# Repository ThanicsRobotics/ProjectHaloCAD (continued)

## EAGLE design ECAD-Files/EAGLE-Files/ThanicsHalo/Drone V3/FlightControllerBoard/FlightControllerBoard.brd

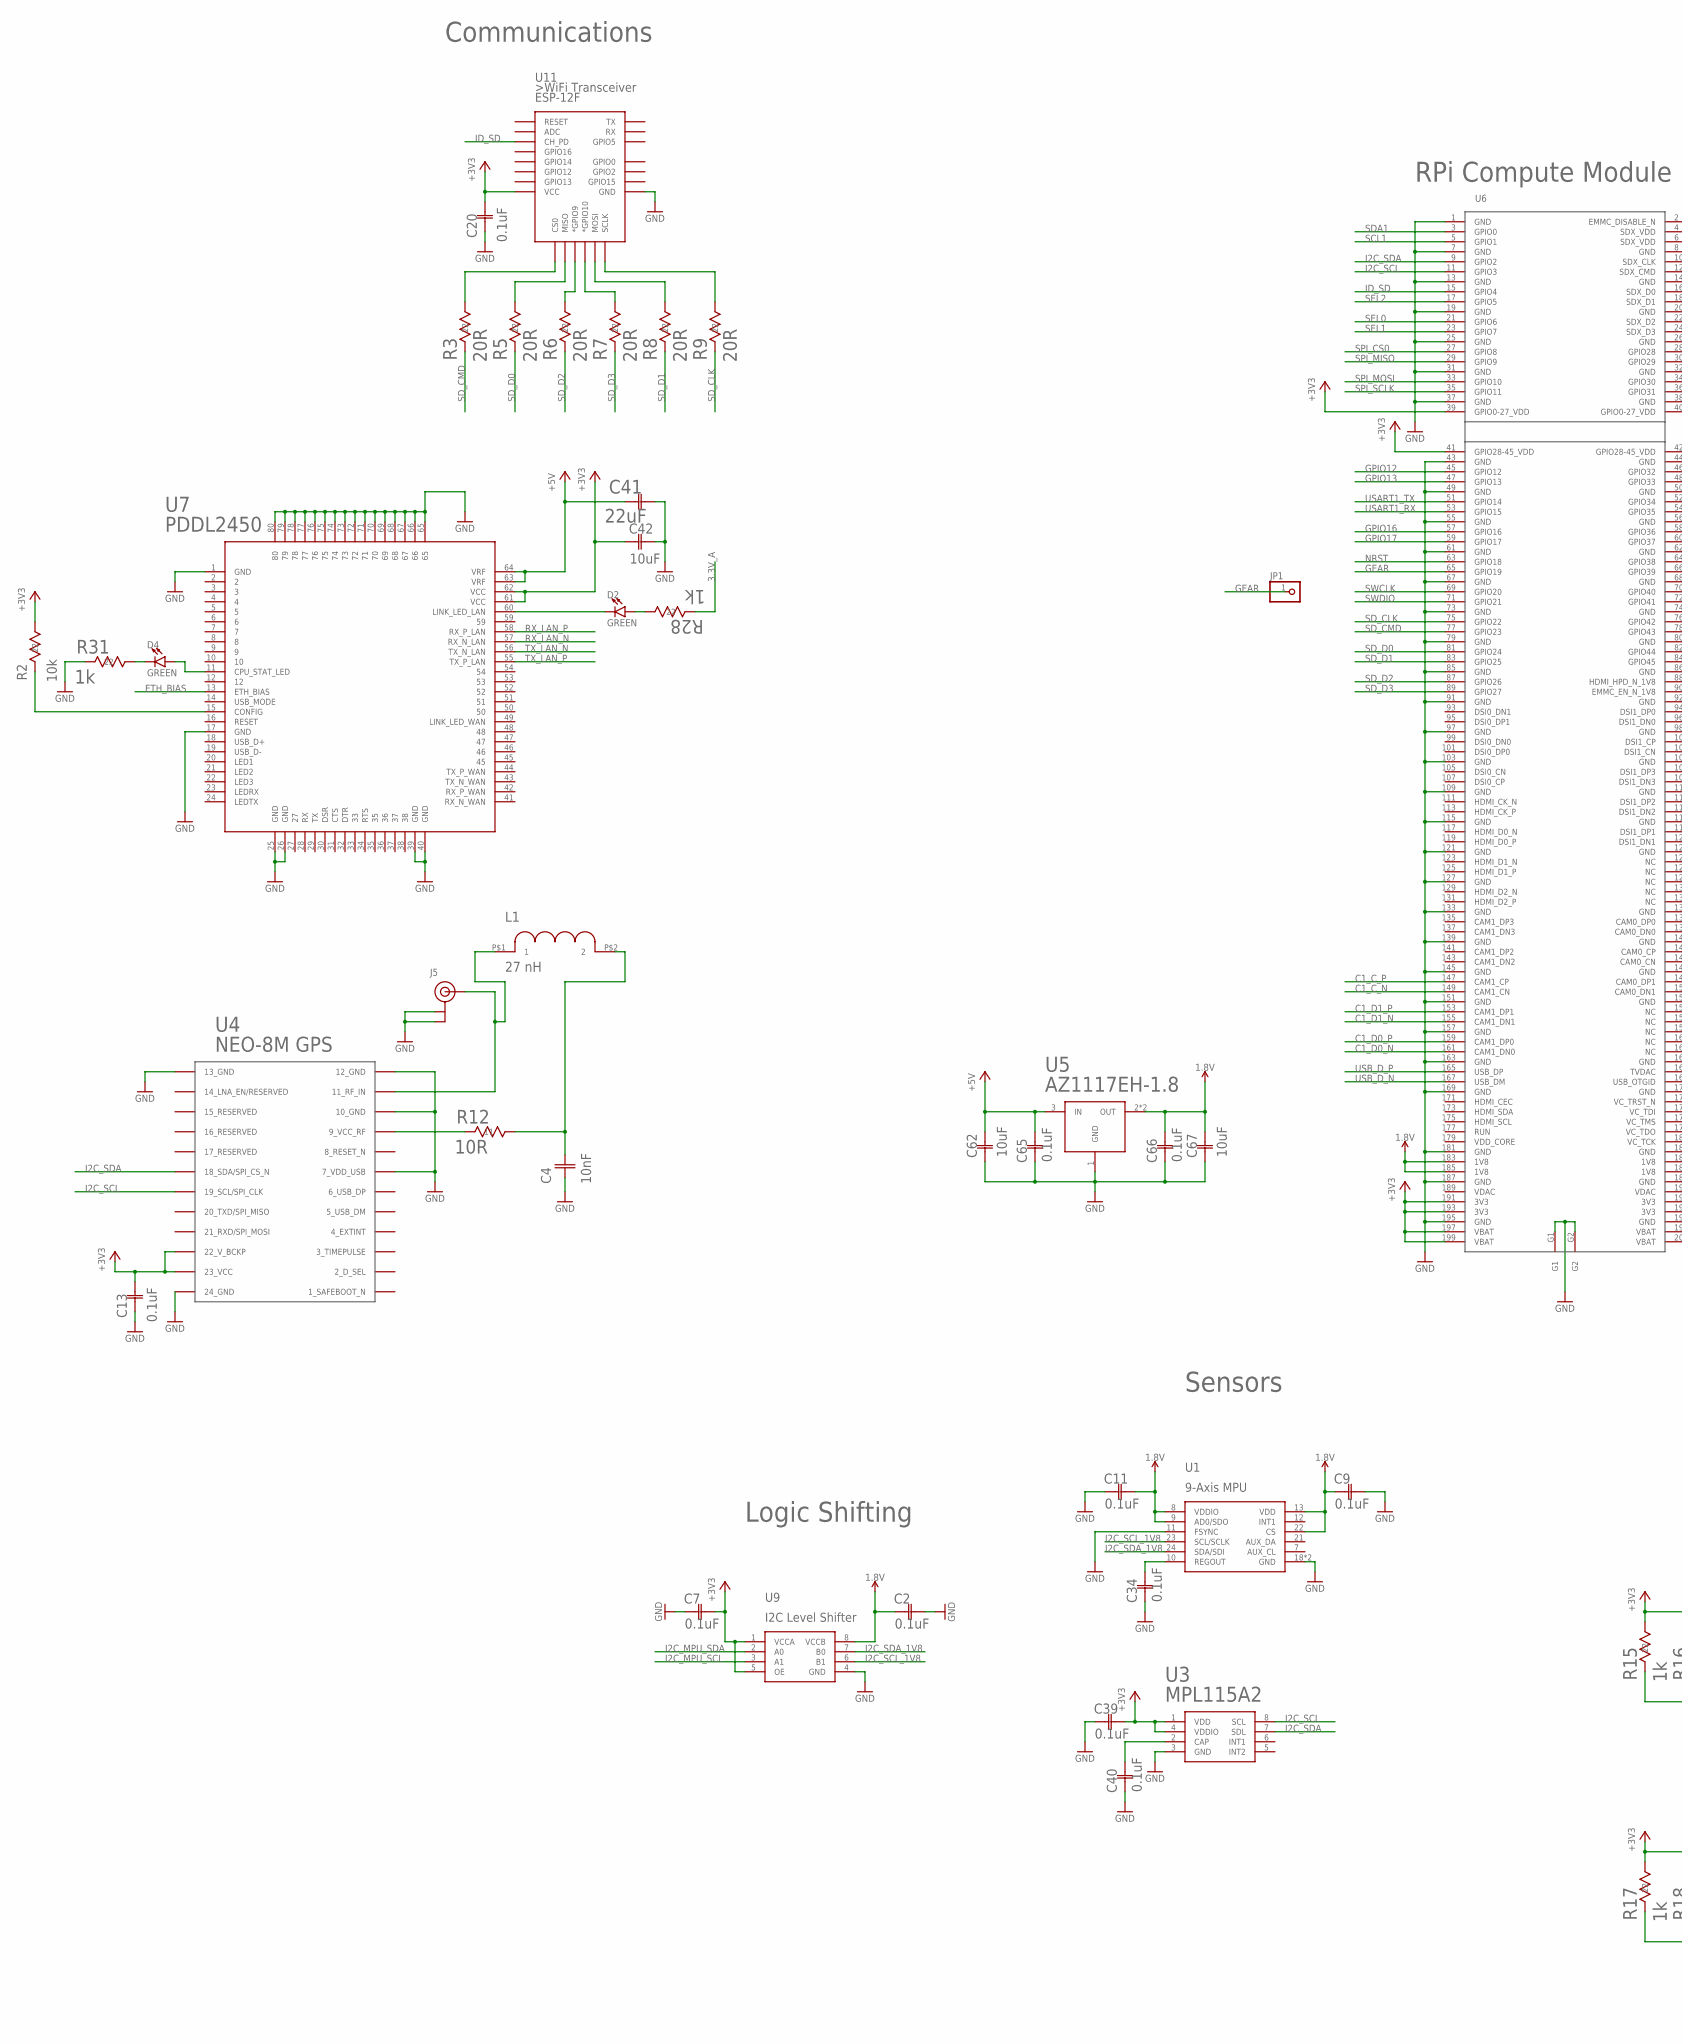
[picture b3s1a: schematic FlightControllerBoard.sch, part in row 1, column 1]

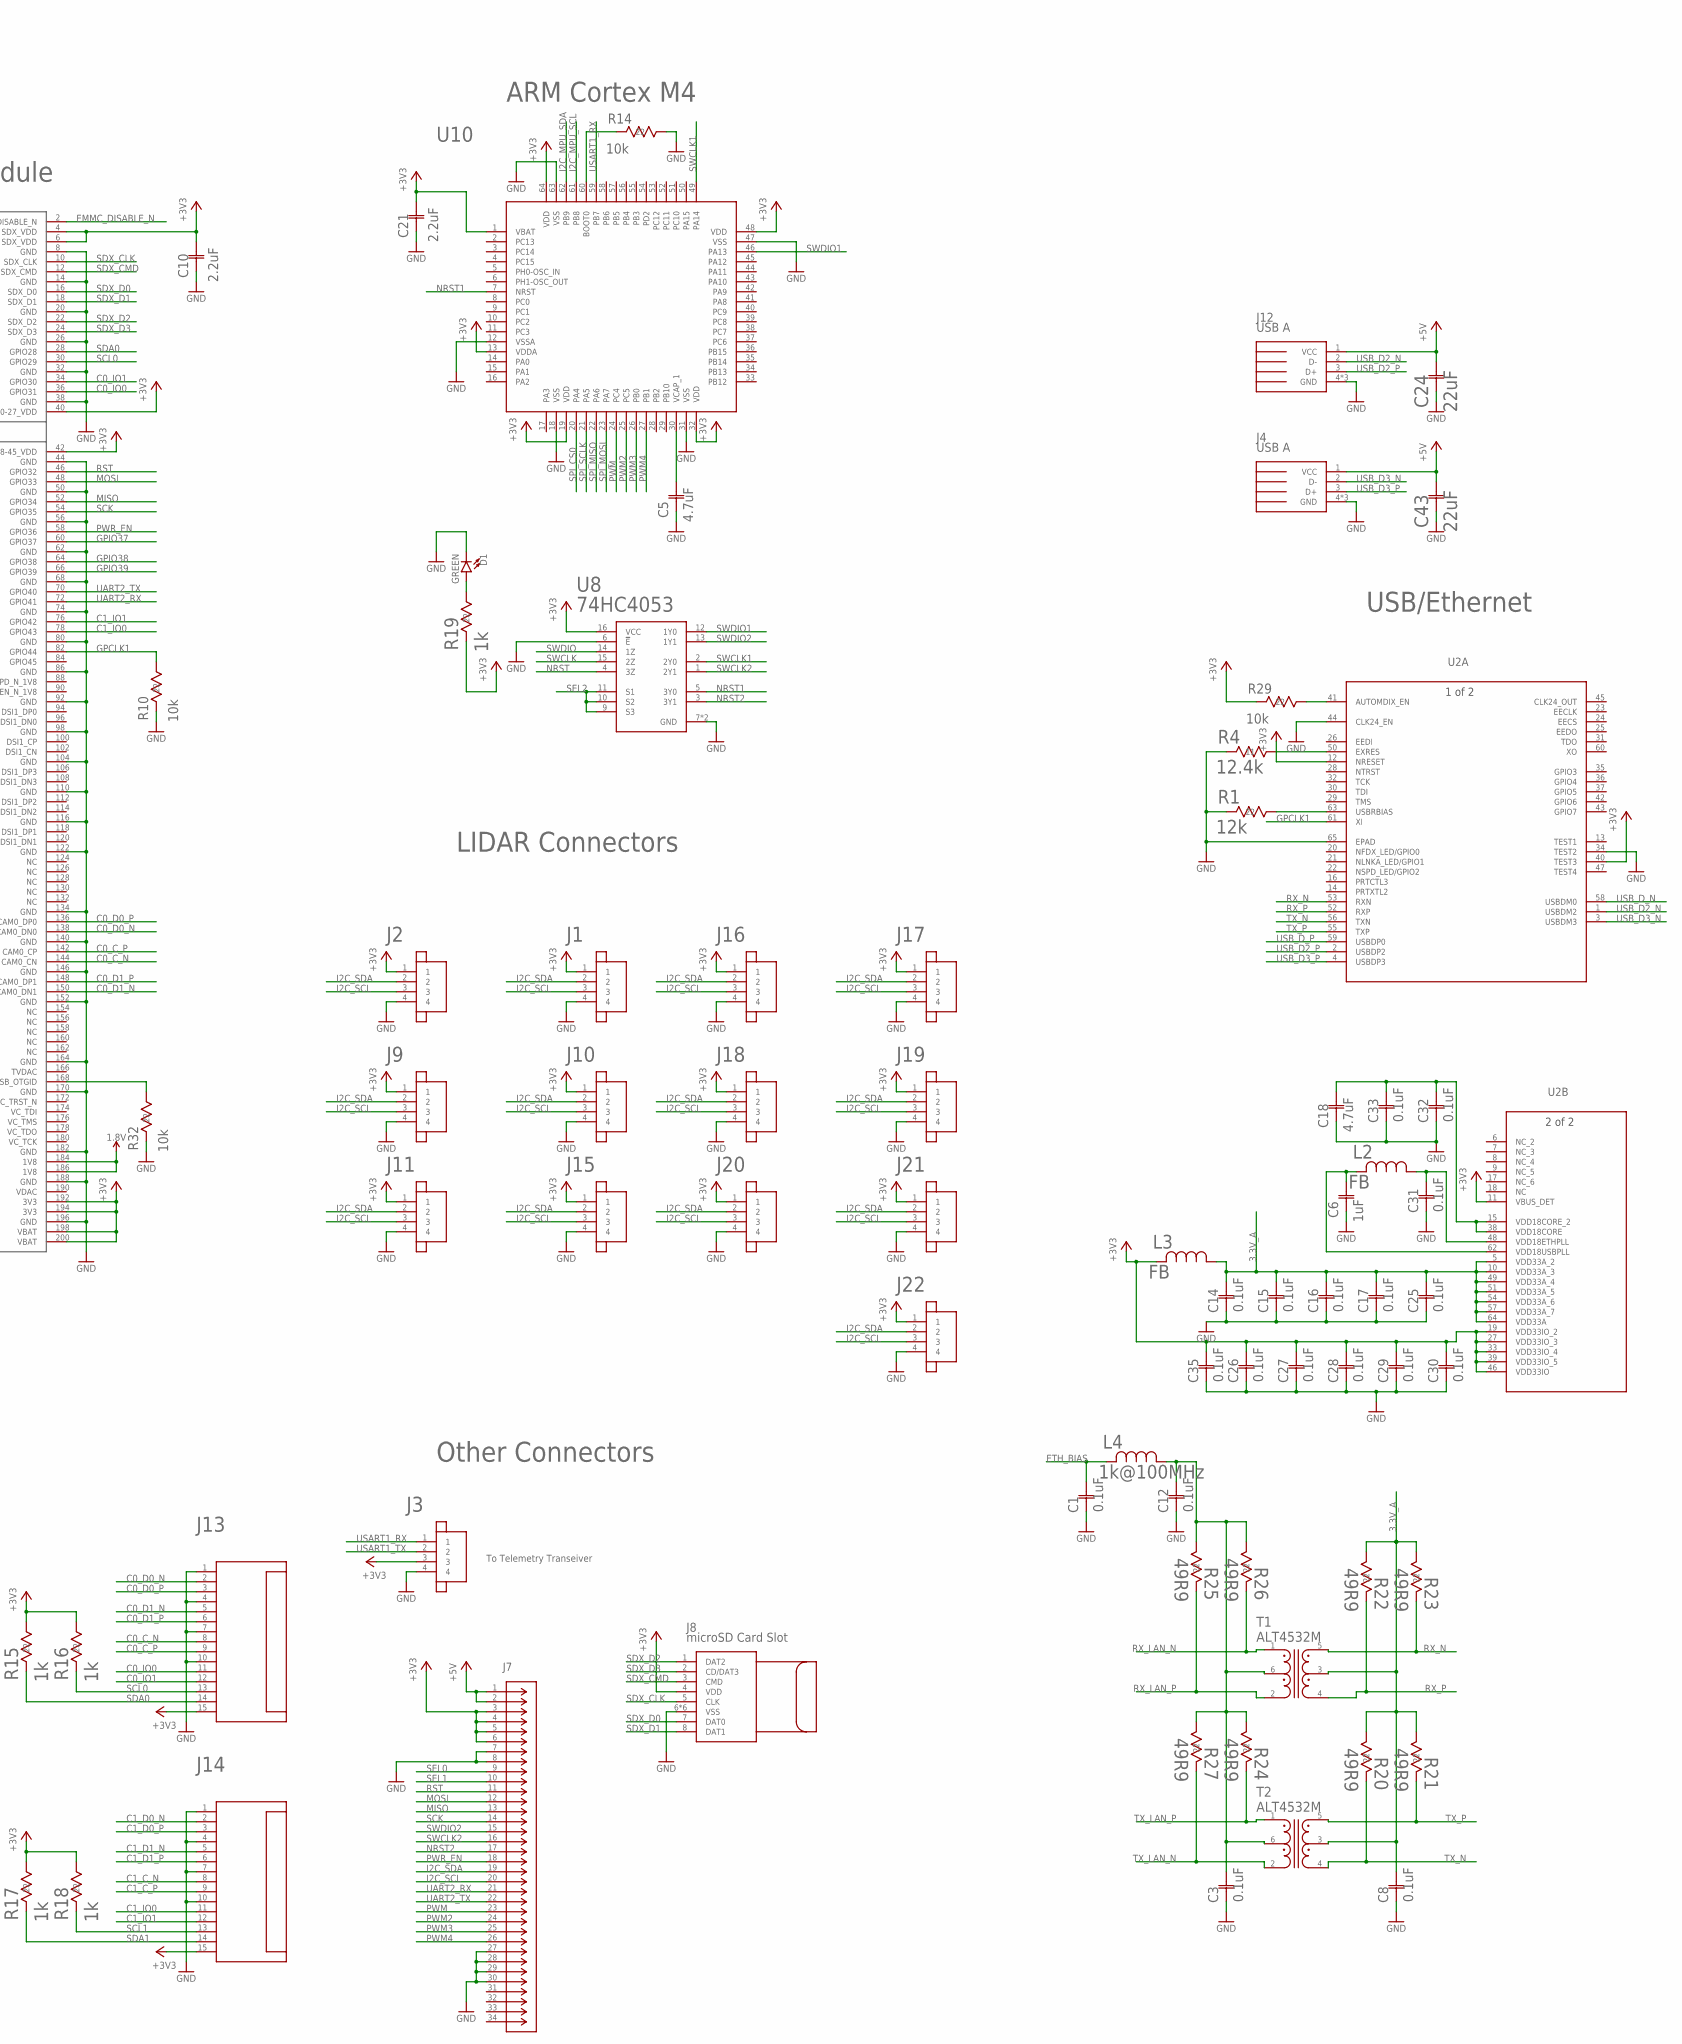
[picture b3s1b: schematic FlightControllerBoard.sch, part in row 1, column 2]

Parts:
C1, C2, C3, C7, C8, C9, C11, C12, C14, C15, C16, C17, C25, C26, C27, C28, C29, C30, C31, C32, C33, C34, C35, C39, C40, C65, C66: 0.1uF; 0402-M
C4: 10nF; 0603_CAPACITOR
C5, C18: 4.7uF; 0603-M
C6: 1uF; YAG_CC0805
C10, C21: 2.2uF; G-188-M
C13, C20: 0.1uF; 0805
C24, C41, C43: 22uF; G-21
C42, C62, C67: 10uF; G-21
D1, D2, D4: GREEN; LED-0603
J1, J2, J3, J9, J10, J11, J15, J16, J17, J18, J19, J20, J21, J22: JST_SH_4POS
J4, J12: UE27AE54100; USBA_RECEPT_VERT
J5: U.FL
J7: 62674-301121ALF; CON30_1X30_DUT_58XF
J8: MICROSD
J13, J14: 0526101572_15ZIF_CONNECTOR; 15POS_FFC_CONNECTOR
JP1: PINHD-1X1; 1X01
L1: 27 nH; 0402_INDUCTOR
L2, L3: FB; IND_BLM18_0603-M
L4: 1k@100MHz; IND_BLM18_0603-M
R1: 12k; RC0402N-M
R2, R10, R14, R29, R32: 10k; RC0603N-M
R3, R5, R6, R7, R8, R9: 20R; RC0603N-M
R4: 12.4k; YAG_R0402-M
R12: 10R; STA_RNCP0805-M
R15, R16, R17, R18, R19, R28, R31: 1k; RC0603N-M
R20, R21, R22, R23, R24, R25, R26, R27: 49R9; RC0402N-M
T1, T2: ALT4532M; ALT4532
U1: ICM-20948; QFN40P300X300X105-25N
U2: LAN9512-JZXQFN64_9X9MC-M; QFN64_9X9MC-M
U3: MPL115A2; LGA8-M
U4: NEO-M8
U5: AZ1117EH-1.8; SOT-223
U6: COMPUTE_MODULE; SO-DIMM
U7: PDDL2450; PDDL2450_SOCKET
U8: 74HC4053; TSSOP16
U9: FXMAR2102; 8-UMLP
U10: STM32F446; LQFP64
U11: ESP12ESMD; ESP12E-SMD

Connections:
1.8V: C2.1, C9.1, C11.2, C66.2, C67.2 (22), U1.8 (VDDIO), U1.9 (AD0/SDO), U1.13 (VDD), U1.22 (CS), U5.2 (OUT), U5.4 (OUT), U6.183 (1V8), U6.184 (1V8), U6.185 (1V8), U6.186 (1V8), U9.8 (VCCB)
3.3V_A: C8.2, C14.2, C15.2, C16.2, C17.2, C25.2, L3.1, R20.1 (11), R21.1 (11), R22.1 (11), R23.1 (11), R28.2 (22), T1.3, T2.3, U2.5 (VDD33A_2), U2.10 (VDD33A_3), U2.49 (VDD33A_4), U2.51 (VDD33A_5), U2.54 (VDD33A_6), U2.57 (VDD33A_7), U2.64 (VDD33A)
+3V3: C7.2, C10.2 (22), C13.2, C20.2, C21.2 (22), C26.2, C27.2, C28.2, C29.2, C30.2, C35.2, C39.2, C42.1 (11), J1.1, J2.1, J3.3, J7.3 (33), J7.4 (44), J7.5 (55), J7.6 (66), J8.4 (VDD), J9.1, J10.1, J11.1, J13.15, J14.15, J15.1, J16.1, J17.1, J18.1, J19.1, J20.1, J21.1, J22.1, L3.2, R2.1 (11), R15.1 (11), R16.1 (11), R17.1 (11), R18.1 (11), R19.2 (22), R29.2 (22), U2.11 (VBUS_DET), U2.12 (NRESET), U2.19 (VDD33IO_2), U2.27 (VDD33IO_3), U2.33 (VDD33IO_4), U2.39 (VDD33IO_5), U2.40 (TEST3), U2.46 (VDD33IO), U3.1 (VDD), U3.4 (VDDIO), U4.22 (22_V_BCKP), U4.23 (23_VCC), U6.4 (SDX_VDD), U6.6 (SDX_VDD), U6.39 (GPIO0-27_VDD), U6.40 (GPIO0-27_VDD), U6.41 (GPIO28-45_VDD), U6.42 (GPIO28-45_VDD), U6.191 (3V3), U6.192 (3V3), U6.193 (3V3), U6.194 (3V3), U6.197 (VBAT), U6.198 (VBAT), U6.199 (VBAT), U6.200 (VBAT), U7.61 (VCC), U7.62 (VCC), U8.16 (VCC), U9.1 (VCCA), U9.5 (OE), U10.1 (VBAT), U10.13 (VDDA), U10.19 (VDD), U10.32 (VDD), U10.48 (VDD), U10.64 (VDD), U11.VCC
+5V: C24.2 (22), C41.1 (11), C43.2 (22), C62.2 (22), C65.2, J4.1 (VCC), J7.1 (11), J7.2 (22), J12.1 (VCC), U5.3 (IN), U7.63 (VRF), U7.64 (VRF)
C0_C_N: J13.8, U6.144 (CAM0_CN)
C0_C_P: J13.9, U6.142 (CAM0_CP)
C0_D0_N: J13.2, U6.138 (CAM0_DN0)
C0_D0_P: J13.3, U6.136 (CAM0_DP0)
C0_D1_N: J13.5, U6.150 (CAM0_DN1)
C0_D1_P: J13.6, U6.148 (CAM0_DP1)
C0_IO0: J13.11, U6.36 (GPIO31)
C0_IO1: J13.12, U6.34 (GPIO30)
C1_C_N: J14.8, U6.149 (CAM1_CN)
C1_C_P: J14.9, U6.147 (CAM1_CP)
C1_D0_N: J14.2, U6.161 (CAM1_DN0)
C1_D0_P: J14.3, U6.159 (CAM1_DP0)
C1_D1_N: J14.5, U6.155 (CAM1_DN1)
C1_D1_P: J14.6, U6.153 (CAM1_DP1)
C1_IO0: J14.11, U6.78 (GPIO43)
C1_IO1: J14.12, U6.76 (GPIO42)
EMMC_DISABLE_N: U6.2 (EMMC_DISABLE_N)
ETH_BIAS: C1.2, L4.2, U7.13 (ETH_BIAS)
GEAR: JP1.1, U6.65 (GPIO19)
GND: C1.1, C2.2, C3.1, C4.1, C5.1, C6.1 (11), C7.1, C8.1, C9.2, C10.1 (11), C11.1, C12.1, C13.1, C14.1, C15.1, C16.1, C17.1, C18.1, C20.1, C21.1 (11), C24.1 (11), C25.1, C26.1, C27.1, C28.1, C29.1, C30.1, C31.1, C32.1, C33.1, C34.1, C35.1, C39.1, C40.1, C41.2 (22), C42.2 (22), C43.1 (11), C62.1 (11), C65.1, C66.1, C67.1 (11), D1.C, J1.4, J2.4, J3.4, J4.4 (GND), J4.P$5 (GND), J4.P$6 (GND), J5.P$1 (GND), J5.P$2 (GND), J7.7 (77), J7.8 (88), J7.27 (2727), J7.28 (2828), J7.29 (2929), J7.30 (3030), J8.6 (VSS), J8.9 (VSS), J8.10 (VSS), J8.11 (VSS), J8.12 (VSS), J8.13 (VSS), J9.4, J10.4, J11.4, J12.4 (GND), J12.P$5 (GND), J12.P$6 (GND), J13.1, J13.4, J13.7, J13.10, J14.1, J14.4, J14.7, J14.10, J15.4, J16.4, J17.4, J18.4, J19.4, J20.4, J21.4, J22.4, R1.2 (22), R4.1 (11), R10.2 (22), R14.1 (11), R31.2 (22), R32.2 (22), U1.11 (FSYNC), U1.18 (GND), U1.20 (GND), U2.34 (TEST2), U2.44 (CLK24_EN), U2.65 (EPAD), U3.3 (GND), U4.7 (7_VDD_USB), U4.10 (10_GND), U4.12 (12_GND), U4.13 (13_GND), U4.24 (24_GND), U5.1 (GND), U6.1 (GND), U6.7 (GND), U6.8 (GND), U6.13 (GND), U6.14 (GND), U6.19 (GND), U6.20 (GND), U6.25 (GND), U6.26 (GND), U6.31 (GND), U6.32 (GND), U6.37 (GND), U6.38 (GND), U6.43 (GND), U6.44 (GND), U6.49 (GND), U6.50 (GND), U6.55 (GND), U6.56 (GND), U6.61 (GND), U6.62 (GND), U6.67 (GND), U6.68 (GND), U6.73 (GND), U6.74 (GND), U6.79 (GND), U6.80 (GND), U6.85 (GND), U6.86 (GND), U6.91 (GND), U6.92 (GND), U6.97 (GND), U6.98 (GND), U6.103 (GND), U6.104 (GND), U6.109 (GND), U6.110 (GND), U6.115 (GND), U6.116 (GND), U6.121 (GND), U6.122 (GND), U6.127 (GND), U6.133 (GND), U6.134 (GND), U6.139 (GND), U6.140 (GND), U6.145 (GND), U6.146 (GND), U6.151 (GND), U6.152 (GND), U6.157 (GND), U6.163 (GND), U6.164 (GND), U6.169 (GND), U6.170 (GND), U6.181 (GND), U6.182 (GND), U6.187 (GND), U6.188 (GND), U6.195 (GND), U6.196 (GND), U6.G1, U6.G2, U7.1 (GND), U7.17 (GND), U7.25 (GND), U7.26 (GND), U7.39 (GND), U7.40 (GND), U7.65, U7.66, U7.67, U7.68, U7.69, U7.70, U7.71, U7.72, U7.73, U7.74, U7.75, U7.76, U7.77, U7.78, U7.79, U7.80, U8.6 (!E), U8.7 (GND), U8.8 (GND), U9.4 (GND), U10.12 (VSSA), U10.18 (VSS), U10.31 (VSS), U10.47 (VSS), U10.63 (VSS), U11.GND
GND1: D2.C, U7.60 (LINK_LED_LAN)
GPCLK1: R10.1 (11), U2.61 (XI), U6.82 (GPIO44)
GPIO12: U6.45 (GPIO12)
GPIO13: U6.47 (GPIO13)
GPIO16: U6.57 (GPIO16)
GPIO17: U6.59 (GPIO17)
GPIO37: U6.60 (GPIO37)
GPIO38: U6.64 (GPIO38)
GPIO39: U6.66 (GPIO39)
I2C_MPU_SCL: U9.3 (A1), U10.61 (PB8)
I2C_MPU_SDA: U9.2 (A0), U10.62 (PB9)
I2C_SCL: J1.3, J2.3, J7.20 (2020), J9.3, J10.3, J11.3, J15.3, J16.3, J17.3, J18.3, J19.3, J20.3, J21.3, J22.3, U3.8 (SCL), U4.19 (19_SCL/SPI_CLK), U6.11 (GPIO3)
I2C_SCL_1V8: U1.23 (SCL/SCLK), U9.6 (B1)
I2C_SDA: J1.2, J2.2, J7.19 (1919), J9.2, J10.2, J11.2, J15.2, J16.2, J17.2, J18.2, J19.2, J20.2, J21.2, J22.2, U3.7 (SDL), U4.18 (18_SDA/SPI_CS_N), U6.9 (GPIO2)
I2C_SDA_1V8: U1.24 (SDA/SDI), U9.7 (B0)
ID_SD: U6.15 (GPIO4), U11.CH_PD
MISO: J7.13 (1313), U6.52 (GPIO34)
MOSI: J7.12 (1212), U6.48 (GPIO33)
unnamed: J5.P$3 (SIGNAL), L1.P$1 (1), U4.11 (11_RF_IN)
unnamed: C34.2, U1.10 (REGOUT)
unnamed: R29.1 (11), U2.41 (AUTOMDIX_EN)
unnamed: D1.A, R19.1 (11)
unnamed: R1.1 (11), U2.63 (USBRBIAS)
unnamed: C40.2, U3.2 (CAP)
unnamed: R3.1 (11), U11.CS0
unnamed: R5.1 (11), U11.MISO
unnamed: R6.1 (11), U11.GPIO9 (*GPIO9)
unnamed: R7.1 (11), U11.GPIO10 (*GPIO10)
unnamed: C5.2, U10.30 (VCAP_1)
unnamed: D2.A, R28.1 (11)
unnamed: R12.1 (11), U4.9 (9_VCC_RF)
unnamed: R8.1 (11), U11.MOSI
unnamed: R9.1 (11), U11.SCLK
unnamed: R14.2 (22), U10.60 (BOOT0)
unnamed: C31.2, L2.1, U2.48 (VDD18ETHPLL)
unnamed: C6.2 (22), L2.2, U2.62 (VDD18USBPLL)
unnamed: R4.2 (22), U2.50 (EXRES)
unnamed: C18.2, C32.2, C33.2, U2.15 (VDD18CORE_2), U2.38 (VDD18CORE)
unnamed: C3.2, C12.2, L4.1, R24.1 (11), R25.1 (11), R26.1 (11), R27.1 (11), T1.6, T2.6
unnamed: R2.2 (22), U7.15 (CONFIG)
unnamed: D4.A, U7.11 (CPU_STAT_LED)
unnamed: C4.2, L1.P$2 (2), R12.2 (22)
unnamed: D4.C, R31.1 (11)
unnamed: R32.1 (11), U6.168 (USB_OTGID)
NRST: U6.63 (GPIO18), U8.4 (3Z)
NRST1: U8.5 (3Y0), U10.7 (NRST)
NRST2: J7.17 (1717), U8.3 (3Y1)
PWM: J7.23 (2323), U10.24 (PC4)
PWM2: J7.24 (2424), U10.25 (PC5)
PWM3: J7.25 (2525), U10.26 (PB0)
PWM4: J7.26 (2626), U10.27 (PB1)
PWR_EN: J7.18 (1818), U6.58 (GPIO36)
RST: J7.11 (1111), U6.46 (GPIO32)
RX_LAN_N: R26.2 (22), T1.1, U7.57 (RX_N_LAN)
RX_LAN_P: R25.2 (22), T1.2, U7.58 (RX_P_LAN)
RX_N: R23.2 (22), T1.5, U2.53 (RXN)
RX_P: R22.2 (22), T1.4, U2.52 (RXP)
SCK: J7.14 (1414), U6.54 (GPIO35)
SCL0: J13.13, R16.2 (22), U6.30 (GPIO29)
SCL1: J14.13, R18.2 (22), U6.5 (GPIO1)
SDA0: J13.14, R15.2 (22), U6.28 (GPIO28)
SDA1: J14.14, R17.2 (22), U6.3 (GPIO0)
SDX_CLK: J8.5 (CLK), U6.10 (SDX_CLK)
SDX_CMD: J8.3 (CMD), U6.12 (SDX_CMD)
SDX_D0: J8.7 (DAT0), U6.16 (SDX_D0)
SDX_D1: J8.8 (DAT1), U6.18 (SDX_D1)
SDX_D2: J8.1 (DAT2), U6.22 (SDX_D2)
SDX_D3: J8.2 (CD/DAT3), U6.24 (SDX_D3)
SD_CLK: R9.2 (22), U6.75 (GPIO22)
SD_CMD: R3.2 (22), U6.77 (GPIO23)
SD_D0: R5.2 (22), U6.81 (GPIO24)
SD_D1: R8.2 (22), U6.83 (GPIO25)
SD_D2: R6.2 (22), U6.87 (GPIO26)
SD_D3: R7.2 (22), U6.89 (GPIO27)
SEL0: J7.9 (99), U6.21 (GPIO6)
SEL1: J7.10 (1010), U6.23 (GPIO7)
SEL2: U6.17 (GPIO5), U8.9 (S3), U8.10 (S2), U8.11 (S1)
SPI_CS0: U6.27 (GPIO8), U10.20 (PA4)
SPI_MISO: U6.29 (GPIO9), U10.22 (PA6)
SPI_MOSI: U6.33 (GPIO10), U10.23 (PA7)
SPI_SCLK: U6.35 (GPIO11), U10.21 (PA5)
SWCLK: U6.69 (GPIO20), U8.15 (2Z)
SWCLK1: U8.2 (2Y0), U10.49 (PA14)
SWCLK2: J7.16 (1616), U8.1 (2Y1)
SWDIO: U6.71 (GPIO21), U8.14 (1Z)
SWDIO1: U8.12 (1Y0), U10.46 (PA13)
SWDIO2: J7.15 (1515), U8.13 (1Y1)
TX_LAN_N: R27.2 (22), T2.2, U7.56 (TX_N_LAN)
TX_LAN_P: R24.2 (22), T2.1, U7.55 (TX_P_LAN)
TX_N: R20.2 (22), T2.4, U2.56 (TXN)
TX_P: R21.2 (22), T2.5, U2.55 (TXP)
UART2_RX: J7.21 (2121), U6.72 (GPIO41)
UART2_TX: J7.22 (2222), U6.70 (GPIO40)
USART1_RX: J3.1, U6.53 (GPIO15), U10.59 (PB7)
USART1_TX: J3.2, U6.51 (GPIO14)
USB_D2_N: J12.2 (D-), U2.1 (USBDM2)
USB_D2_P: J12.3 (D+), U2.2 (USBDP2)
USB_D3_N: J4.2 (D-), U2.3 (USBDM3)
USB_D3_P: J4.3 (D+), U2.4 (USBDP3)
USB_D_N: U2.58 (USBDM0), U6.167 (USB_DM)
USB_D_P: U2.59 (USBDP0), U6.165 (USB_DP)

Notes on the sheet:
To Telemetry Transeiver
Communications
RPi Compute Module
Sensors
LIDAR Connectors
Logic Shifting
ARM Cortex M4
USB/Ethernet
Other Connectors

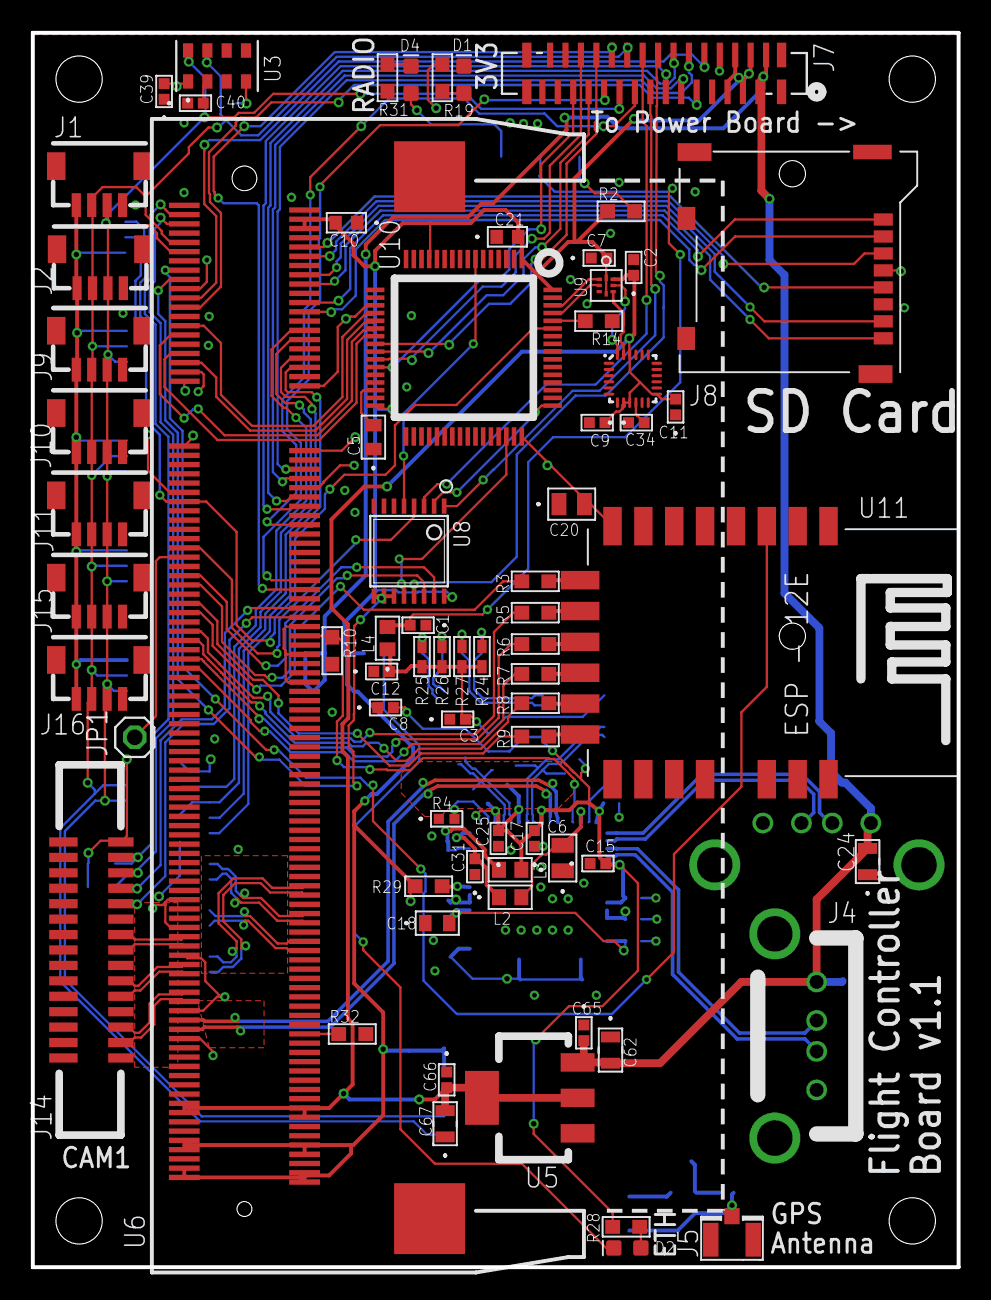
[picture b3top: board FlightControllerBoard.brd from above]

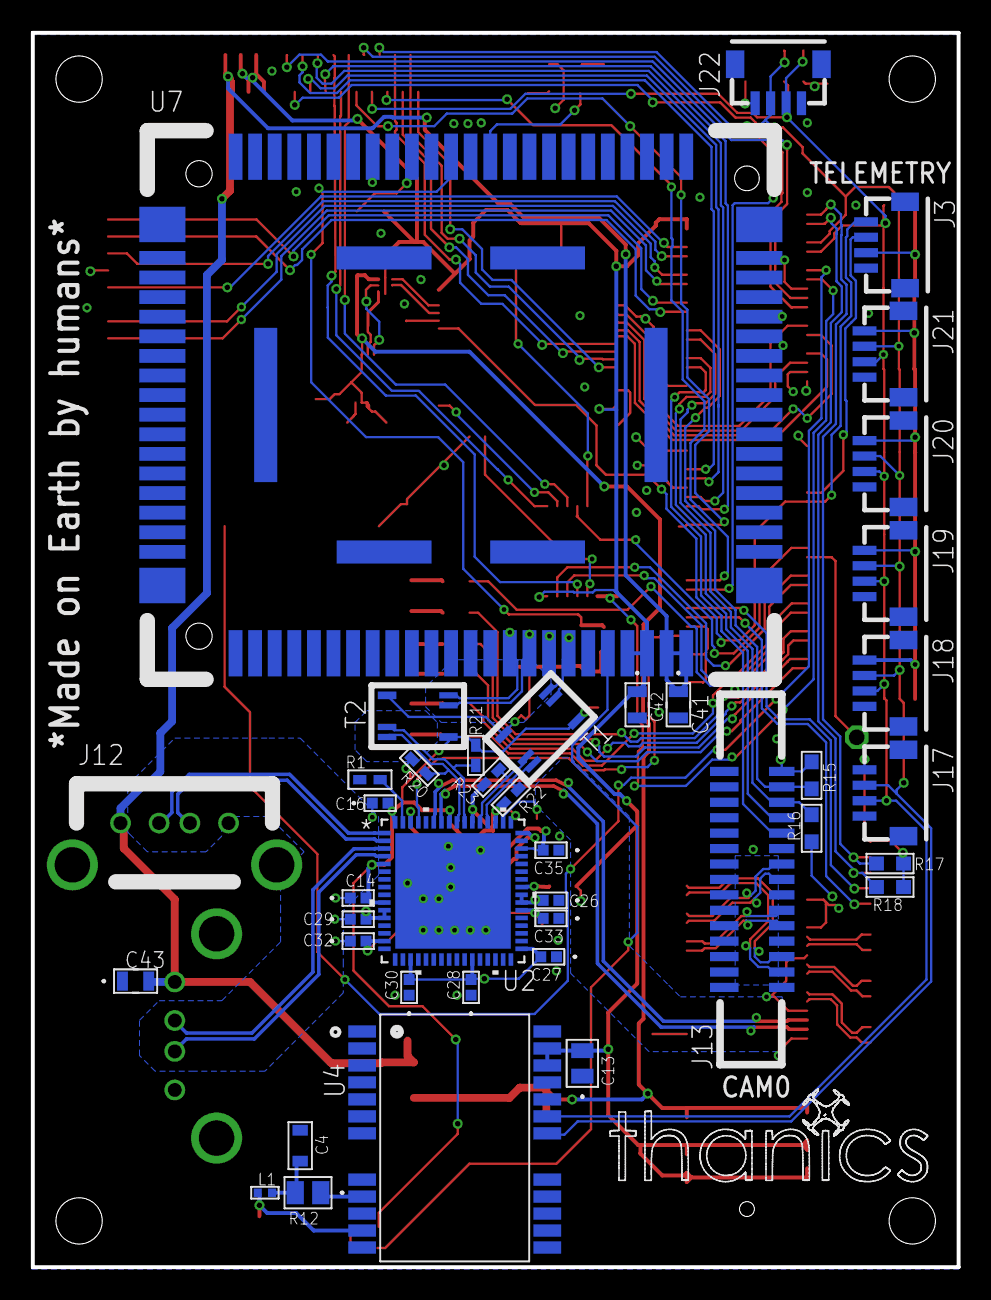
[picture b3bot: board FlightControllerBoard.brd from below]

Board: 4 copper layers, 60.0 x 80.0 mm, 112 parts (40 on the bottom side), 117 nets.

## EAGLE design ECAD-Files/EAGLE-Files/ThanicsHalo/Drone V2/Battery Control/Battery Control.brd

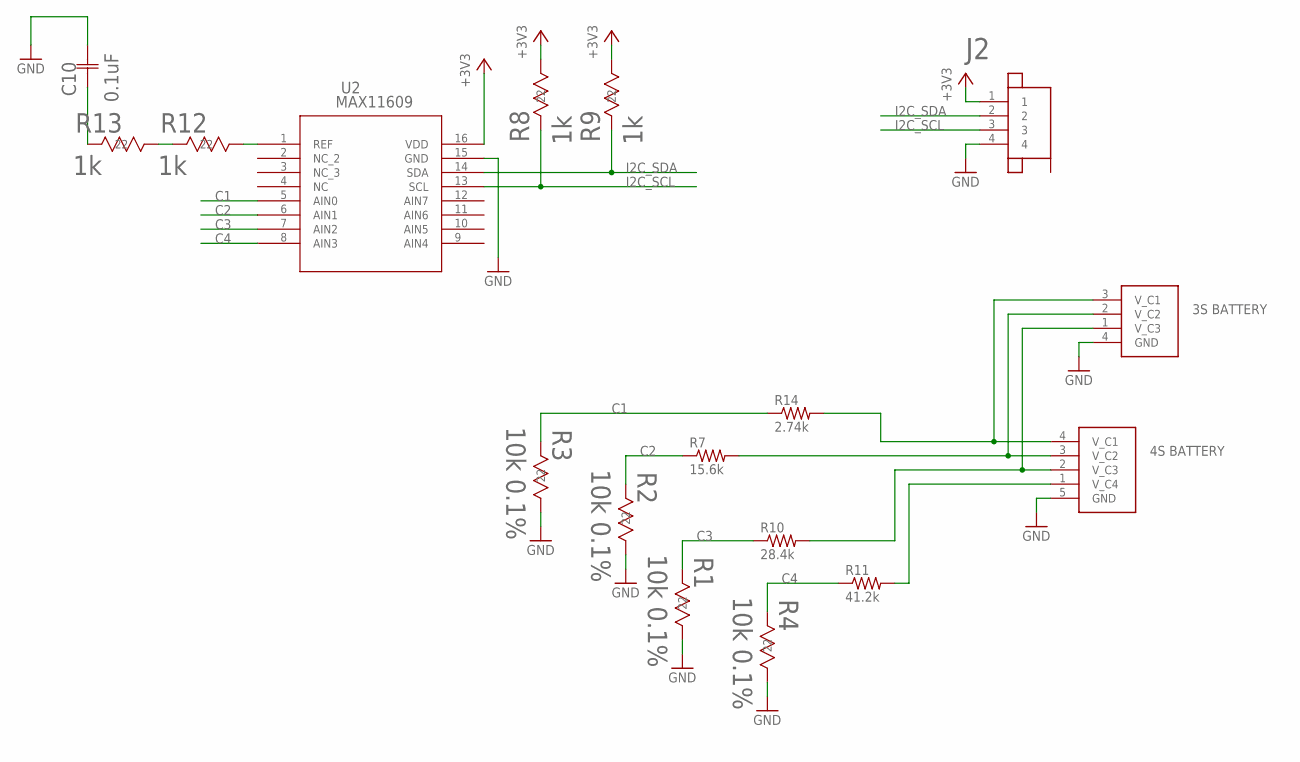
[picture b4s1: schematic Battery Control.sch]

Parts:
C10: 0.1uF; 0805
J1: JST-XH_4POS
J2: JST_SH_4POS
J3: JST-XH_5POS
R1, R2, R3, R4: 10k 0.1%; RC0805N
R7: 15.6k; R0402
R8, R9, R12, R13: 1k; RC0603N-M
R10: 28.4k; R0603
R11: 41.2k; R0603
R14: 2.74k; R0603
U2: MAX11608EEE+21-0055H_16-M; 21-0055H_16-M

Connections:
+3V3: J2.1, R8.1 (11), R9.1 (11), U2.16 (VDD)
C1: R3.2 (22), R14.1, U2.5 (AIN0)
C2: R2.2 (22), R7.1, U2.6 (AIN1)
C3: R1.2 (22), R10.1, U2.7 (AIN2)
C4: R4.2 (22), R11.1, U2.8 (AIN3)
GND: C10.2, J1.4 (GND), J2.4, J3.5 (GND), R1.1 (11), R2.1 (11), R3.1 (11), R4.1 (11), U2.15 (GND)
I2C_SCL: J2.3, R8.2 (22), U2.13 (SCL)
I2C_SDA: J2.2, R9.2 (22), U2.14 (SDA)
unnamed: R12.1 (11), U2.1 (REF)
unnamed: J1.3 (V_C1), J3.4 (V_C1), R14.2
unnamed: J1.2 (V_C2), J3.3 (V_C2), R7.2
unnamed: J1.1 (V_C3), J3.2 (V_C3), R10.2
unnamed: J3.1 (V_C4), R11.2
unnamed: R12.2 (22), R13.1 (11)
unnamed: C10.1, R13.2 (22)

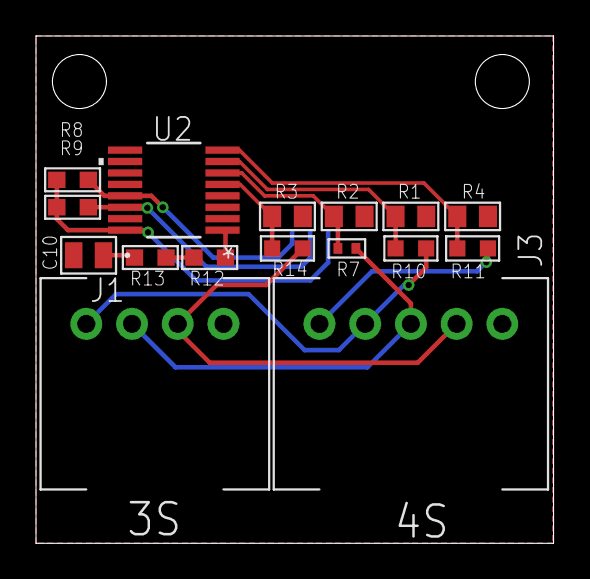
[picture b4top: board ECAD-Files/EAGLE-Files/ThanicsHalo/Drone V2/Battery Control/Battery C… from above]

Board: 2 copper layers, 28.8 x 28.2 mm, 17 parts (1 on the bottom side), 15 nets.

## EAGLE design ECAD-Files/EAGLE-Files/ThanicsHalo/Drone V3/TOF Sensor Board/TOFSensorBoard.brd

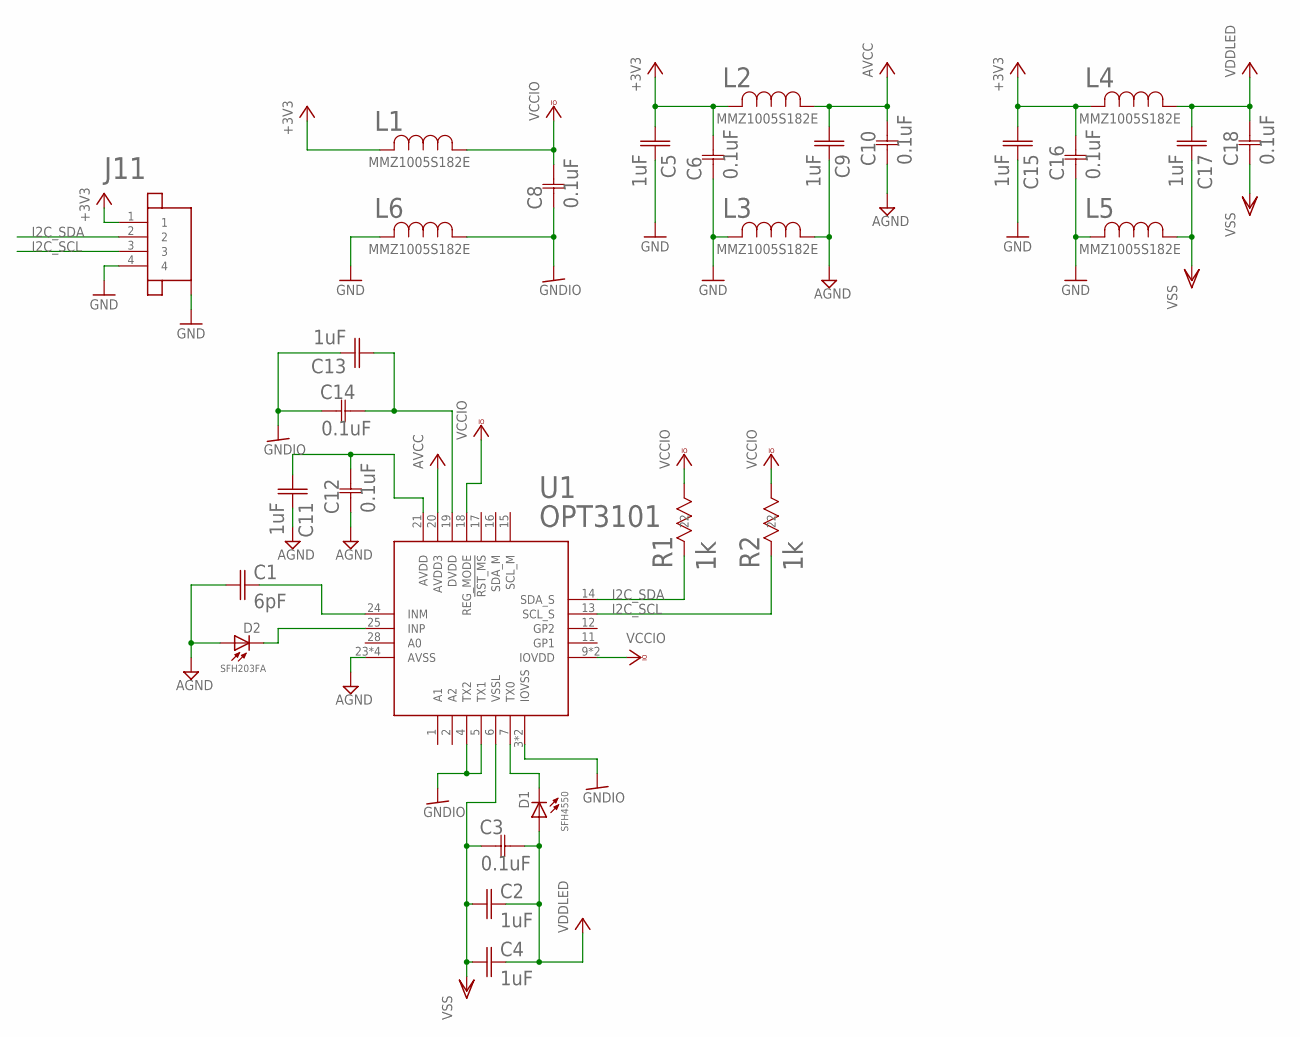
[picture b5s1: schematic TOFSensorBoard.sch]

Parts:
C1: 6pF; 0402_CAPACITOR
C2, C4, C5, C9, C11, C13, C15, C17: 1uF; 0603_CAPACITOR
C3, C6, C8, C10, C12, C14, C16, C18: 0.1uF; 0402-M
D1: SFH4550; 5MM_LED
D2: SFH203FA; 5MM_LED
J11: JST_SH_4POS
L1, L2, L3, L4, L5, L6: MMZ1005S182ET000IND_1005-M; IND_1005-M
R1, R2: 1k; RC0603N-M
U1: OPT3101; 28-VQFN

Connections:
+3V1: C13.1, C14.2, U1.19 (DVDD)
+3V3: C5.1, C6.2, C15.1, C16.2, J11.1, L1.2, L2.2, L4.2
AGND: C1.1, C9.2, C10.1, C11.2, C12.1, D2.A, L3.1, U1.23 (AVSS), U1.26 (AVSS), U1.27 (AVSS), U1.29 (AVSS)
AVCC: C9.1, C10.2, L2.1, U1.20 (AVDD3)
GND: C5.2, C6.1, C15.2, C16.1, J11.4, J11.P$5 (5), J11.P$6 (5), L3.2, L5.2, L6.2
GNDIO: C8.1, C13.2, C14.1, L6.1, U1.3 (IOVSS), U1.4 (TX2), U1.5 (TX1), U1.8 (IOVSS)
I2C_SCL: J11.3, R2.2 (22), U1.13 (SCL_S)
I2C_SDA: J11.2, R1.2 (22), U1.14 (SDA_S)
unnamed: C11.1, C12.2, U1.21 (AVDD)
unnamed: D1.C, U1.7 (TX0)
unnamed: C1.2, U1.24 (INM)
unnamed: D2.C, U1.25 (INP)
VCCIO: C8.2, L1.1, R1.1 (11), R2.1 (11), U1.9 (IOVDD), U1.10 (IOVDD), U1.18 (REG_MODE)
VDDLED: C2.2, C3.2, C4.2, C17.1, C18.2, D1.A, L4.1
VSS: C2.1, C3.1, C4.1, C17.2, C18.1, L5.1, U1.6 (VSSL)

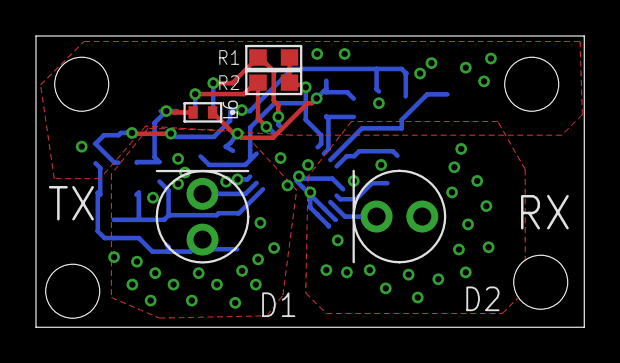
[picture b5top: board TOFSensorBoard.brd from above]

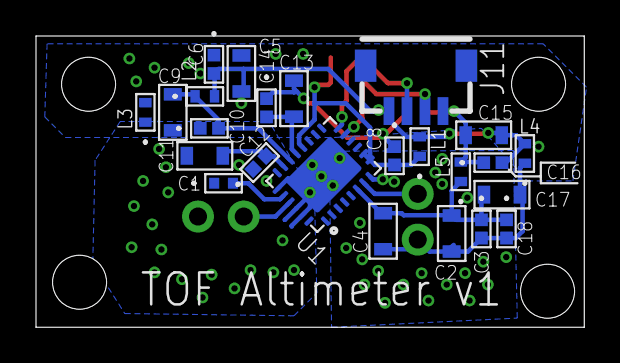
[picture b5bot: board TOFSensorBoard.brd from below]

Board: 4 copper layers, 30.5 x 16.2 mm, 29 parts (24 on the bottom side), 15 nets.

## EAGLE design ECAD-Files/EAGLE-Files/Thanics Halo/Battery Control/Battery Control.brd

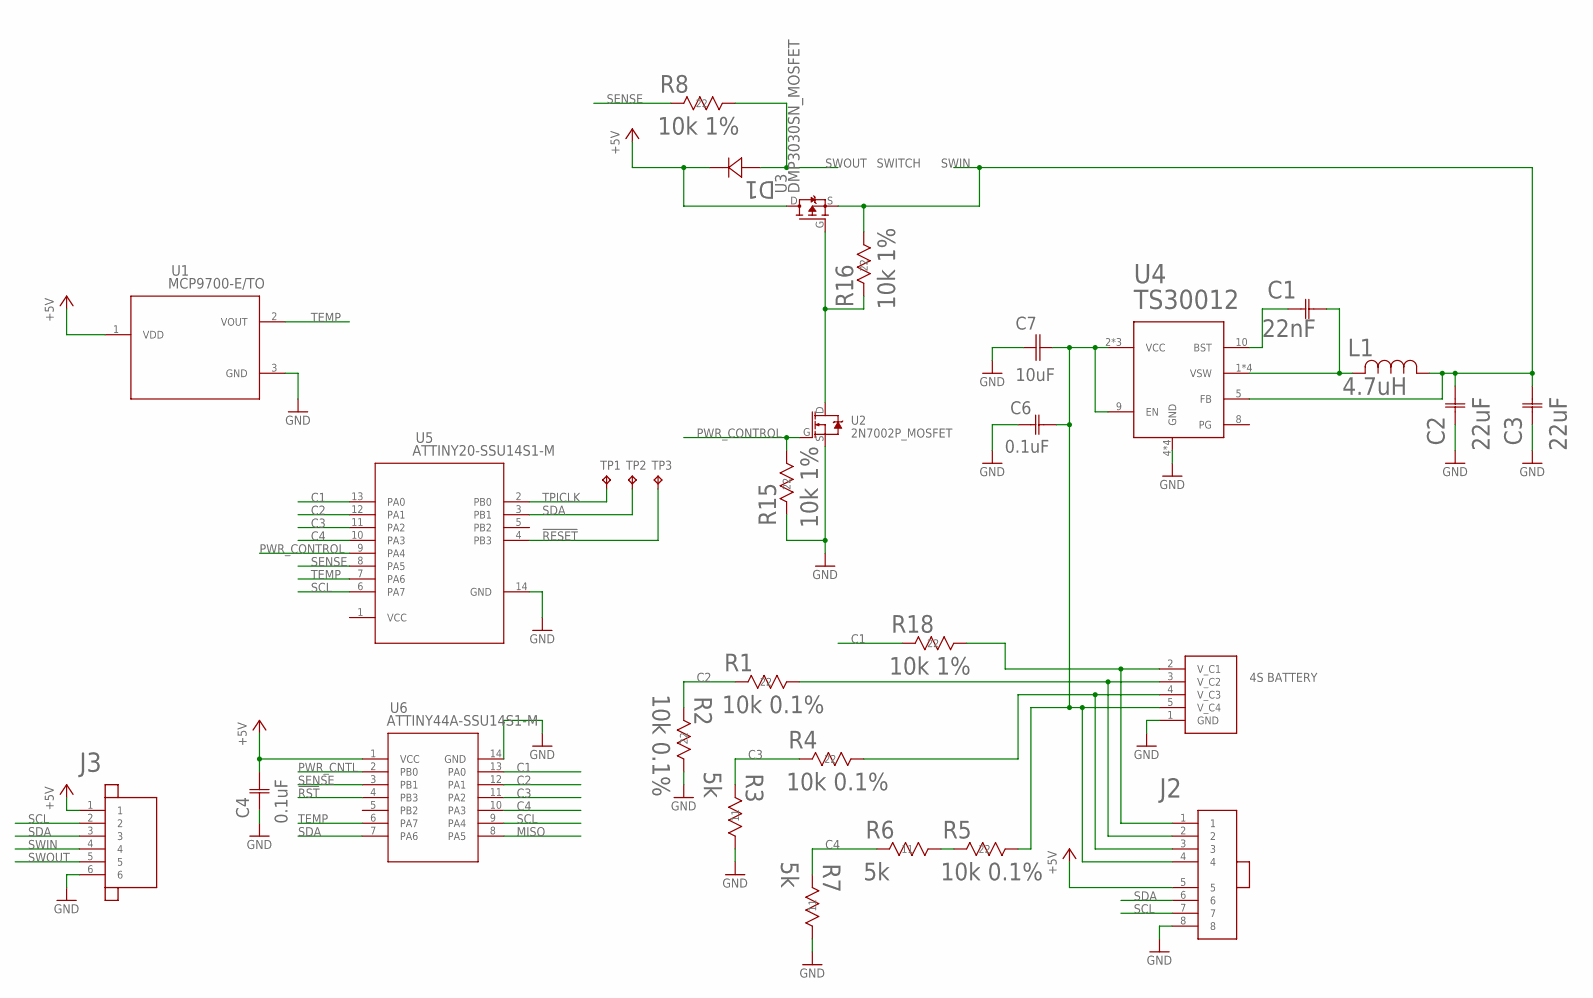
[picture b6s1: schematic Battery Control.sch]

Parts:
C1: 22nF; G-155-M
C2, C3: 22uF; G-21
C4, C6: 0.1uF; 0805
C7: 10uF; 1206_MLCC
D1: 1N4148W-7-FSOD123-M; SOD123-M
J1: JST-XH_5POS
J2: SPRING_BTB_8POS_FEMALE
J3: JST_SH_6POS_SIDE
L1: 4.7uH; 1008
R1, R2, R4, R5: 10k 0.1%; RC0805N
R3, R6, R7: 5k; 0402
R8, R15, R16, R18: 10k 1%; RC0805N
TP1, TP2, TP3: TPB2,54; B2,54
U1: MCP9700-E/TO; TO-92_MC
U2: 2N7002P_MOSFET; SOT-23_(TO-236AB)
U3: DMP3030SN_MOSFET; SC59_MOSFET
U4: TS30012; 16-VQFN
U5: ATTINY20-SSU14S1-M; 14S1-M
U6: ATTINY44A-SSU14S1-M; 14S1-M

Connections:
!RESET: TP3.TP, U5.4 (PB3)
!RST: U6.4 (PB3)
+5V: C4.2, D1.C (12), J2.5, J3.1, U1.1 (VDD), U3.D, U6.1 (VCC)
C1: R18.2 (22), U5.13 (PA0), U6.13 (PA0)
C2: R1.2 (22), R2.2 (22), U5.12 (PA1), U6.12 (PA1)
C3: R3.1 (11), R4.2 (22), U5.11 (PA2), U6.11 (PA2)
C4: R6.1 (11), R7.1 (11), U5.10 (PA3), U6.10 (PA3)
GND: C2.1 (11), C3.1 (11), C4.1, C6.1, C7.P$1 (1), J1.1 (GND), J2.8, J3.6, R2.1 (11), R3.2 (22), R7.2 (22), R15.2 (22), U1.3 (GND), U2.S, U4.4 (GND), U4.14 (GND), U4.15 (GND), U4.17 (GND), U5.14 (GND), U6.14 (GND)
MISO: U6.8 (PA5)
unnamed: R16.2 (22), U2.D, U3.G
unnamed: C1.1 (11), U4.10 (BST)
unnamed: C1.2 (22), L1.P$2 (2), U4.1 (VSW), U4.12 (VSW), U4.13 (VSW), U4.16 (VSW)
unnamed: J1.2 (V_C1), J2.1, R18.1 (11)
unnamed: J1.3 (V_C2), J2.2, R1.1 (11)
unnamed: J1.4 (V_C3), J2.3, R4.1 (11)
unnamed: R5.2 (22), R6.2 (22)
unnamed: C6.2, C7.P$2 (2), J1.5 (V_C4), J2.4, R5.1 (11), U4.2 (VCC), U4.3 (VCC), U4.9 (EN), U4.11 (VCC)
PWR_CNTL: U6.2 (PB0)
PWR_CONTROL: R15.1 (11), U2.G, U5.9 (PA4)
SCL: J2.7, J3.2, U5.6 (PA7), U6.9 (PA4)
SDA: J2.6, J3.3, TP2.TP, U5.3 (PB1), U6.7 (PA6)
SENSE: R8.2 (22), U5.8 (PA5), U6.3 (PB1)
SWIN: C2.2 (22), C3.2 (22), J3.4, L1.P$1 (1), R16.1 (11), U3.S, U4.5 (FB)
SWOUT: D1.A (21), J3.5, R8.1 (11)
TEMP: U1.2 (VOUT), U5.7 (PA6), U6.6 (PA7)
TPICLK: TP1.TP, U5.2 (PB0)

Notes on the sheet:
SWITCH
